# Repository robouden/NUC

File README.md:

# NUC project
An addon for NUC series computers. With custom fan controller.

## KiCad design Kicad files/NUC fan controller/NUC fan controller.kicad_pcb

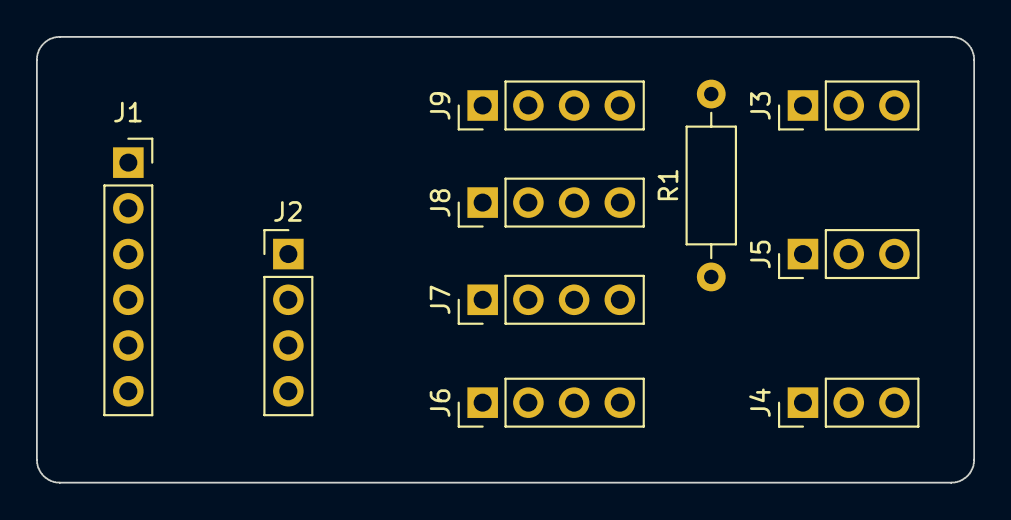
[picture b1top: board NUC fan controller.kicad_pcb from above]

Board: 2 copper layers, 52.1 x 24.8 mm, 10 parts (0 on the bottom side), 8 nets, no tracks yet.

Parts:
J1: M5Atom left; PinSocket_1x06_P2.54mm_Vertical
J2: M5Atom right; PinHeader_1x04_P2.54mm_Vertical
J3: sensor 1 connector; PinHeader_1x03_P2.54mm_Vertical
J4: sensor 2 connector; PinHeader_1x03_P2.54mm_Vertical
J5: sensor 3 connector; PinHeader_1x03_P2.54mm_Vertical
J6: Fan 1; PinHeader_1x04_P2.54mm_Vertical
J7: Fan 2; PinHeader_1x04_P2.54mm_Vertical
J8: Fan 3; PinHeader_1x04_P2.54mm_Vertical
J9: Fan 4; PinHeader_1x04_P2.54mm_Vertical
R1: 4.7k; R_Axial_DIN0207_L6.3mm_D2.5mm_P10.16mm_Horizontal

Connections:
/+5V: J2.3, J3.1, J4.1, J5.1, J6.3, J7.3, J8.3, J9.3, R1.2
/PWM: J2.2, J6.2, J7.2, J8.2, J9.2
GND: J2.4, J3.2, J4.2, J5.2, J6.4, J7.4, J8.4, J9.4
unnamed: J1.2, J3.3, J4.3, J5.3, R1.1
unnamed: J1.3, J9.1
unnamed: J1.4, J8.1
unnamed: J1.5, J7.1
unnamed: J2.1, J6.1

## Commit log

2021-07-13 Init
2021-07-13 Created schematic
2021-07-14 Updated schematic
2021-07-14 Cleanup
2021-07-15 Added sensor connectors
2021-07-27 Removed extra resistors for schematic and replaced it with software pullups
2021-07-29 Added software pullup on tacho pin. (less resistors needed)
2021-08-01 Updated code for temperature measurement
2021-08-03 added adjusted temperature for testing speed/temperature
2021-08-03 Added more details for serial monitoring
2021-08-03 Cleanup code
